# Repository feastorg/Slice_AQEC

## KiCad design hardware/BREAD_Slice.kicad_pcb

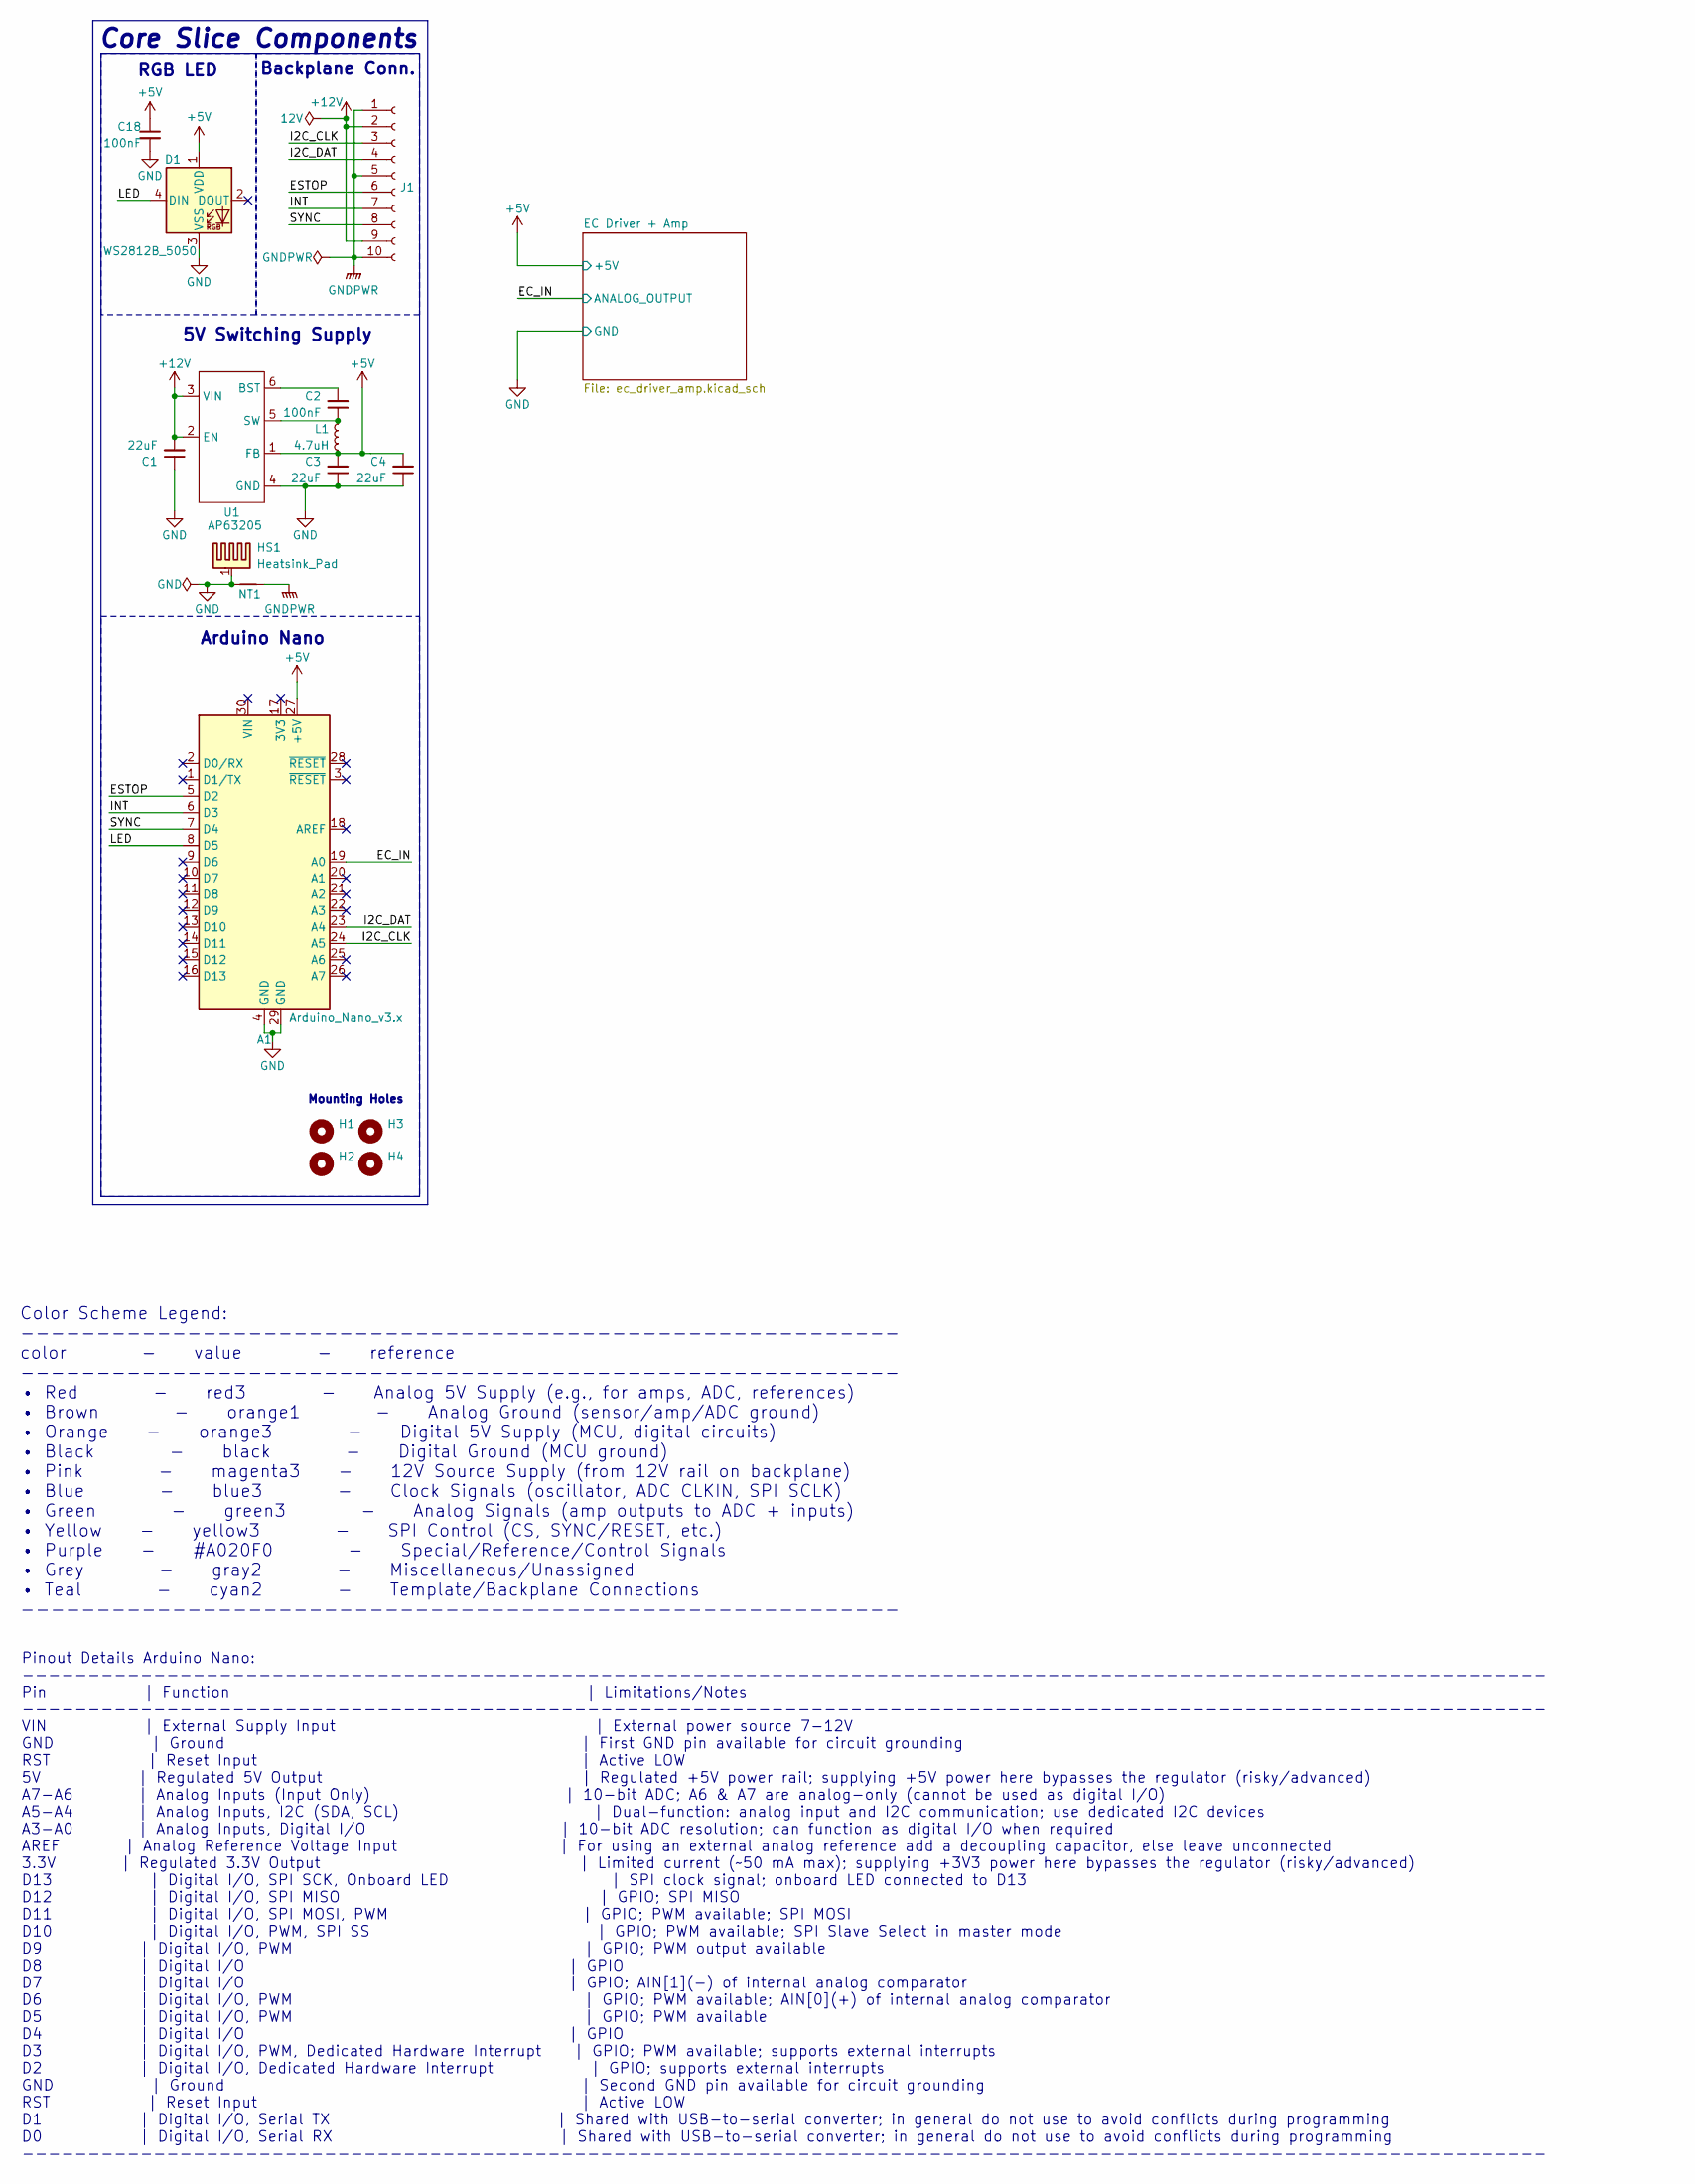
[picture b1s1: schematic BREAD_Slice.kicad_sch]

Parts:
A1: Arduino_Nano_v3.x; Arduino_Nano
C1, C3, C4: 22uF; C_1206_3216Metric
C2: 100nF; C_1206_3216Metric
C18: 100nF; C_0805_2012Metric_Pad1.18x1.45mm_HandSolder
D1: WS2812B_5050; WS2812-5050-4PIN
H1, H2, H3, H4: MountingHole; MountingHole_5mm
HS1: Heatsink_Pad; Thermal_Pad
J1: Conn_01x10_Female; PinSocket_1x10_P2.54mm_Horizontal
L1: 4.7uH; L_1210_3225Metric
NT1: NetTie_2; NetTie-2_SMD_Pad2.0mm
U1: AP63205; TSOT-23-6

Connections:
+5V: A1.27 (+5V), C3.2, C4.2, C18.1, D1.1 (VDD), L1.2, U1.1 (FB); also elsewhere on the board
+12V: C1.2, J1.2, J1.9, U1.2 (EN), U1.3 (VIN)
/EC_IN: A1.19 (A0); also elsewhere on the board
/ESTOP: A1.5 (D2), J1.6
/I2C_CLK: A1.24 (A5), J1.3
/I2C_DAT: A1.23 (A4), J1.4
/INT: A1.6 (D3), J1.7
/LED: A1.8 (D5), D1.4 (DIN)
/SYNC: A1.7 (D4), J1.8
GND: A1.4 (GND), A1.29 (GND), C1.1, C3.1, C4.1, C18.2, D1.3 (VSS), HS1.1, NT1.1, U1.4 (GND); also elsewhere on the board
GNDPWR: J1.1, J1.5, J1.10, NT1.2
unnamed: C2.2, U1.6 (BST)
unnamed: C2.1, L1.1, U1.5 (SW)

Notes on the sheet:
5V Switching Supply
Pinout Details Arduino Nano: -------------------------------------------------------------------------------------------------------------------- Pin | Function | Limitations/Notes -------------------------------------------------------------------------------------------------------------------- V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
RGB LED
Color Scheme Legend: ---------------------------------------------------------- color - value - reference ---------------------------------------------------------- • Red - red3 - Analog 5V Supply (e.g., for amps, ADC, references) • Brown - orange1 - Analog Ground (sensor/amp/ADC ground) • Orange -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
Core Slice Components
Arduino Nano
Mounting Holes
Backplane Conn.

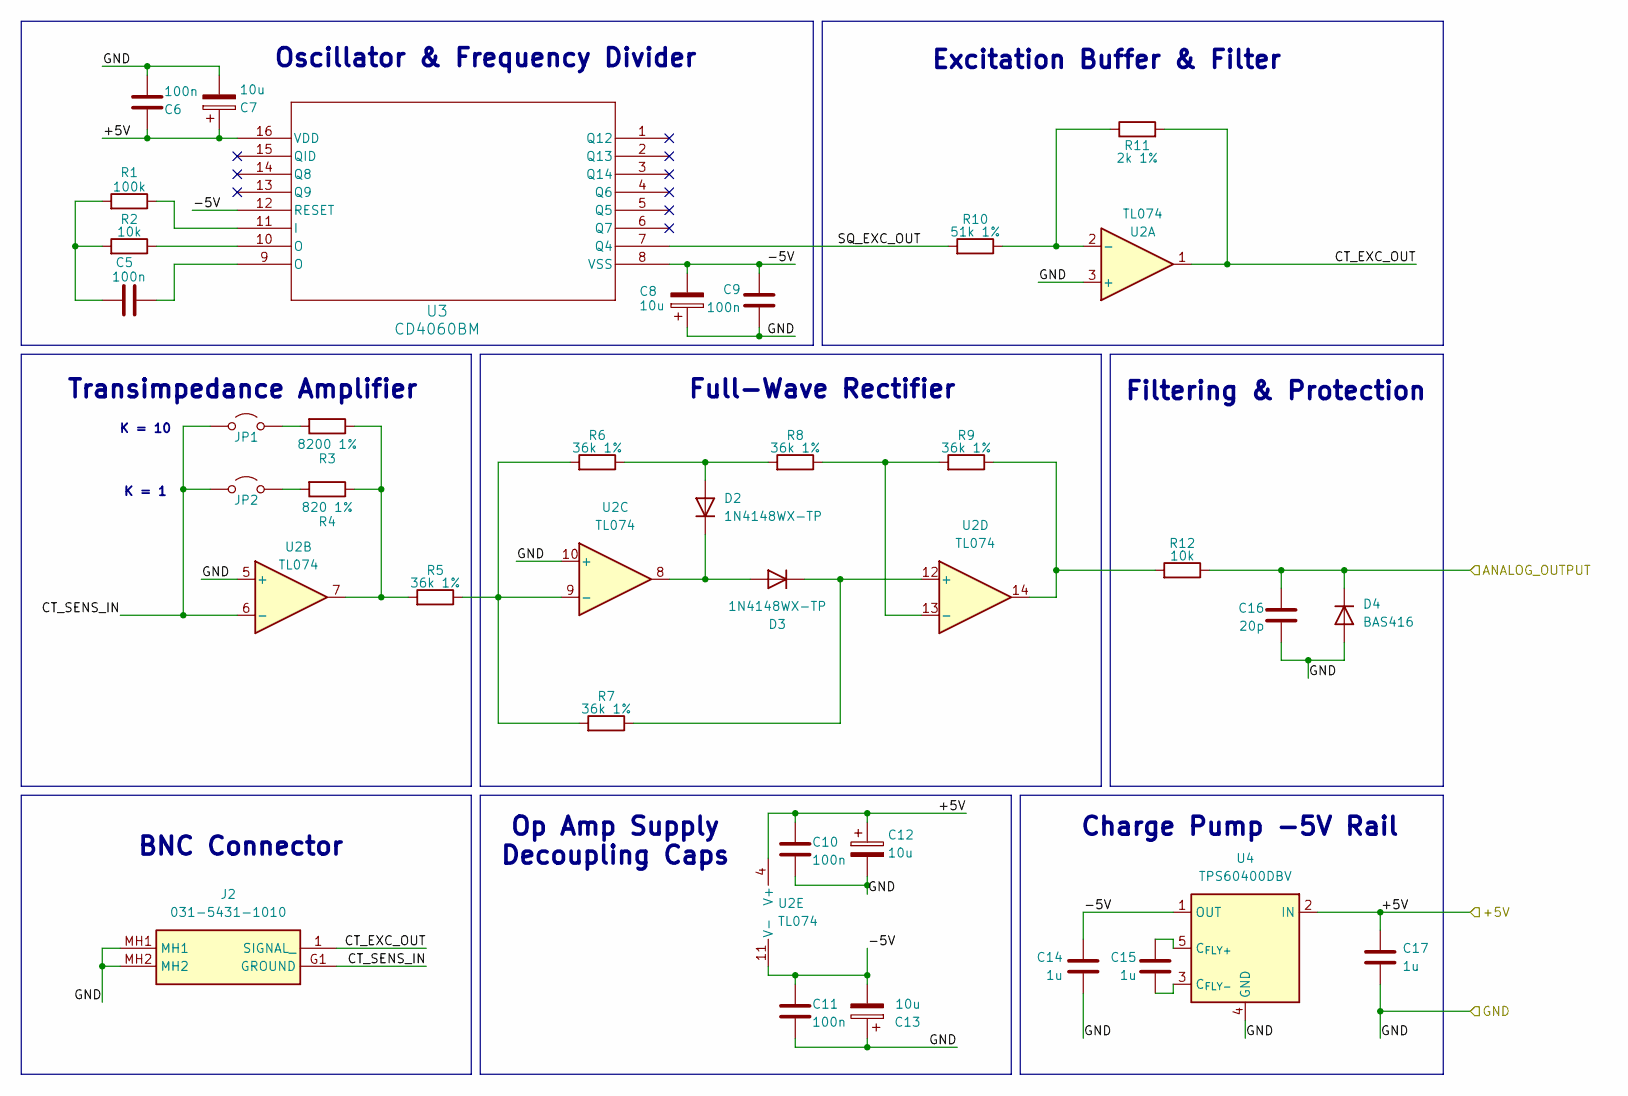
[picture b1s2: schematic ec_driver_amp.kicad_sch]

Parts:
C5, C6, C9, C10, C11: 100n; C_0805_2012Metric_Pad1.18x1.45mm_HandSolder
C7, C8, C12, C13: 10u; C_0805_2012Metric_Pad1.18x1.45mm_HandSolder
C14, C15, C17: 1u; C_0805_2012Metric_Pad1.18x1.45mm_HandSolder
C16: 20p; C_0805_2012Metric_Pad1.18x1.45mm_HandSolder
D2, D3: 1N4148WX-TP; D_SOD-323_HandSoldering
D4: BAS416; D_SOD-323_HandSoldering
J2: 031-5431-1010; 03154311010; Mouser Part Number 523-31-5431-1010
JP1, JP2: Jumper_2_Open; SolderJumper-2_P1.3mm_Open_TrianglePad1.0x1.5mm
R1: 100k; R_0805_2012Metric_Pad1.20x1.40mm_HandSolder
R2, R12: 10k; R_0805_2012Metric_Pad1.20x1.40mm_HandSolder
R3: 8200 1%; R_0805_2012Metric_Pad1.20x1.40mm_HandSolder
R4: 820 1%; R_0805_2012Metric_Pad1.20x1.40mm_HandSolder
R5, R6, R7, R8, R9: 36k 1%; R_0805_2012Metric_Pad1.20x1.40mm_HandSolder
R10: 51k 1%; R_0805_2012Metric_Pad1.20x1.40mm_HandSolder
R11: 2k 1%; R_0805_2012Metric_Pad1.20x1.40mm_HandSolder
U2: TL074; SOIC-14_3.9x8.7mm_P1.27mm
U3: CD4060BM; CD4060-L
U4: TPS60400DBV; SOT-23-5

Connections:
+5V: C6.1, C7.1, C10.1, C12.1, C17.1, U2.4 (V+), U3.16 (VDD), U4.2 (IN); also elsewhere on the board
/EC Driver + Amp/-5V: C8.2, C9.1, C11.1, C13.2, C14.1, U2.11 (V-), U3.8 (VSS), U3.12 (RESET), U4.1 (OUT)
/EC Driver + Amp/CT_EXC_OUT: J2.1 (SIGNAL_), R11.2, U2.1
/EC Driver + Amp/CT_SENS_IN: J2.G1 (GROUND), JP1.1 (A), JP2.1 (A), U2.6 (-)
/EC Driver + Amp/SQ_EXC_OUT: R10.2, U3.7 (Q4)
/EC_IN: C16.1, D4.1 (K), R12.1; also elsewhere on the board
GND: C6.2, C7.2, C8.1, C9.2, C10.2, C11.2, C12.2, C13.1, C14.2, C16.2, C17.2, D4.2 (A), J2.MH1, J2.MH2, U2.3 (+), U2.5 (+), U2.10 (+), U4.4 (GND); also elsewhere on the board
unnamed: C5.1, U3.9 (O)
unnamed: C5.2, R1.2, R2.2
unnamed: D2.2 (A), R6.1, R8.2
unnamed: D2.1 (K), D3.2 (A), U2.8
unnamed: D3.1 (K), R7.1, U2.12 (+)
unnamed: JP1.2 (B), R3.2
unnamed: JP2.2 (B), R4.2
unnamed: R2.1, U3.10 (O)
unnamed: R3.1, R4.1, R5.2, U2.7
unnamed: R9.1, R12.2, U2.14
unnamed: R10.1, R11.1, U2.2 (-)
unnamed: R5.1, R6.2, R7.2, U2.9 (-)
unnamed: R8.1, R9.2, U2.13 (-)
unnamed: R1.1, U3.11 (I)
unnamed: C15.1, U4.5 (C_{FLY+})
unnamed: C15.2, U4.3 (C_{FLY-})

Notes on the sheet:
K = 1
Charge Pump -5V Rail
K = 10
Transimpedance Amplifier
Filtering & Protection
Excitation Buffer & Filter
Op Amp Supply Decoupling Caps
BNC Connector
Oscillator & Frequency Divider
Full-Wave Rectifier

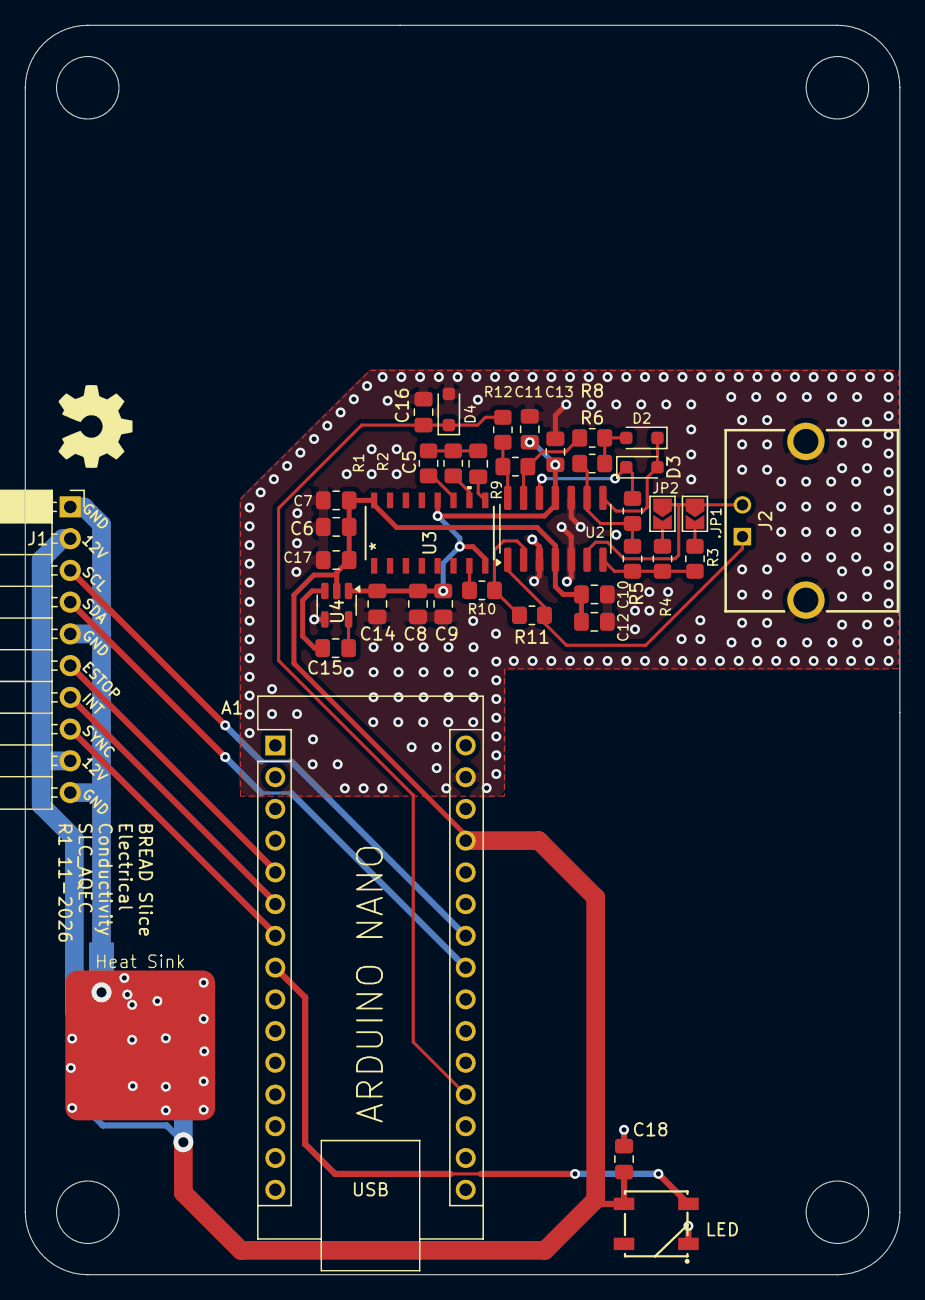
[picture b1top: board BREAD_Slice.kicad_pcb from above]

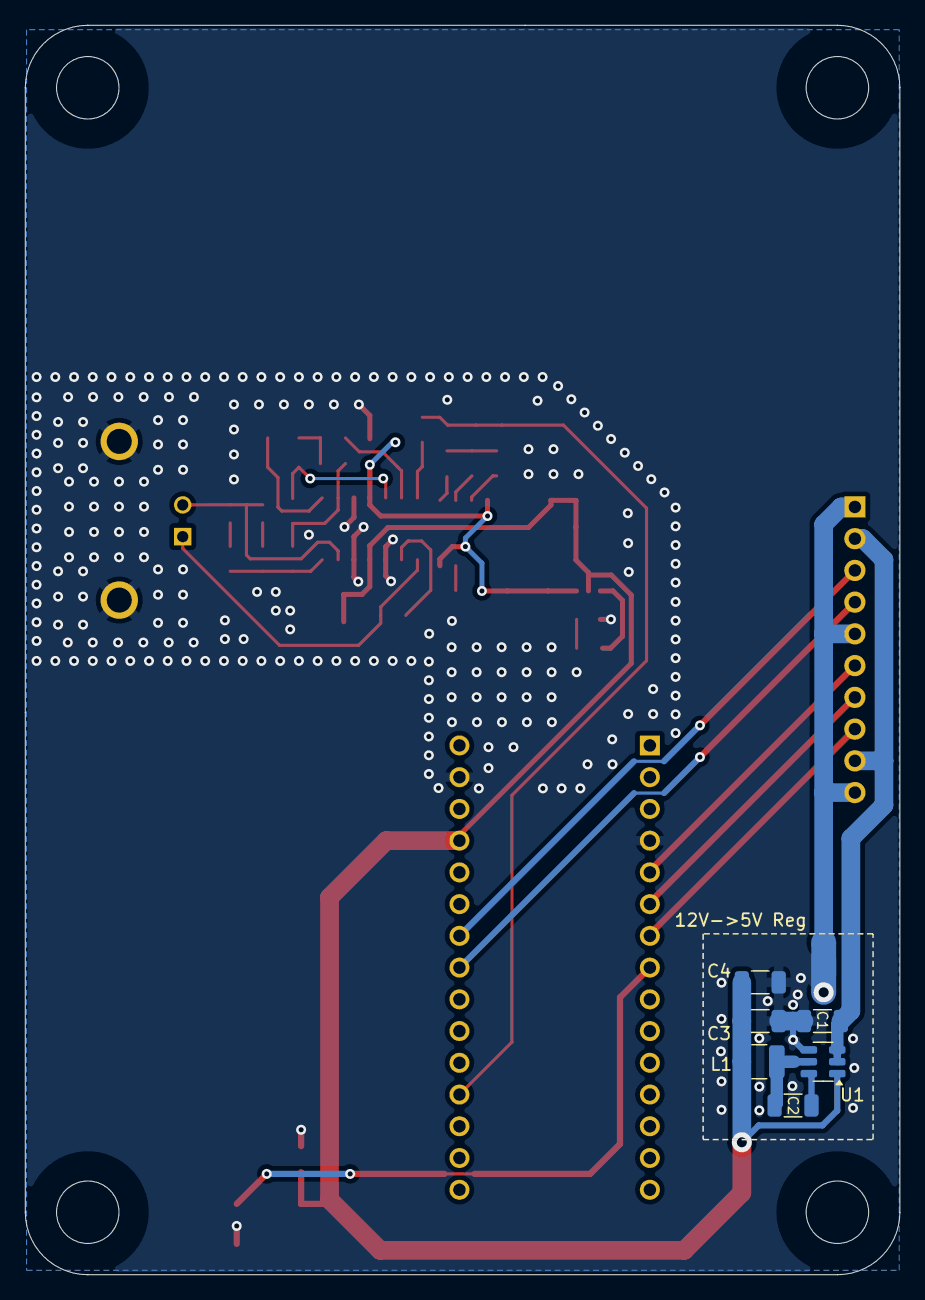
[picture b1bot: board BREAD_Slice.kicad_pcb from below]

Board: 2 copper layers, 70.0 x 100.0 mm, 51 parts (7 on the bottom side), 33 nets.

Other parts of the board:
Logo1: Logo_Open_Hardware_Small; OSHW-Symbol_6.7x6mm_SilkScreen

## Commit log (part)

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2025-04-16 initial commit, completed schematic and board
2025-04-19 minor tweaks
2026-04-18 chore: minor update
2026-05-20 Add slice.yaml manifest (schema v1.0)
2026-05-24 Add KiBot/docs pipeline
2026-05-24 📄 KiBot index + board renders (auto)
2026-05-24 TODO: all CI green
